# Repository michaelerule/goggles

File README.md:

# Goggles

Firmware and documentation for flicker-phosphene hallucination goggles. Some of the content here can be rendered as HTML, and a browsable website version of this repository can be [accessed through Github pages](https://michaelerule.github.io/goggles/).

This material follows earlier [blog posts](http://wealoneonearth.blogspot.co.uk/2009/09/how-to-build-goggles.html) outlining construction of do-it-yourself goggles to demonstrate the [flicker phosphene](http://journals.plos.org/ploscompbiol/article?id=10.1371/journal.pcbi.1002158) hallucination effect. A small batch of a [simplified re-design using welding goggles](http://treehovse.blogspot.co.uk) was produced a few years ago. 

Unless otherwise specified, media, text, and rendered outputs are licensed under the [Creative Commons Attribution Share Alike 4.0 license](https://choosealicense.com/licenses/cc-by-sa-4.0/) (CC BY-SA 4.0). Source code is licensed under the [GNU General Public License version 3.0](https://www.gnu.org/copyleft/gpl.html) (GPLv3). The CC BY-SA 4.0 is [one-way compatible](https://creativecommons.org/compatiblelicenses) with the GPLv3 license. The intent of this licensing choice is to encourage academic norms for citation and attribution. 

This project is published in the spirit (but not the letter) of the [tongue-and-cheek CRAPL license for academic code](http://matt.might.net/articles/crapl/CRAPL-LICENSE.txt). This is not a legal license as it contains internal inconsistencies (like forbidding users to exist). However, it contains a strong caution that this project has not been reviewed or prepared for use by the general public. If there is community interest in a specific subset of the project, please open an issue for improving the organization and documentation.

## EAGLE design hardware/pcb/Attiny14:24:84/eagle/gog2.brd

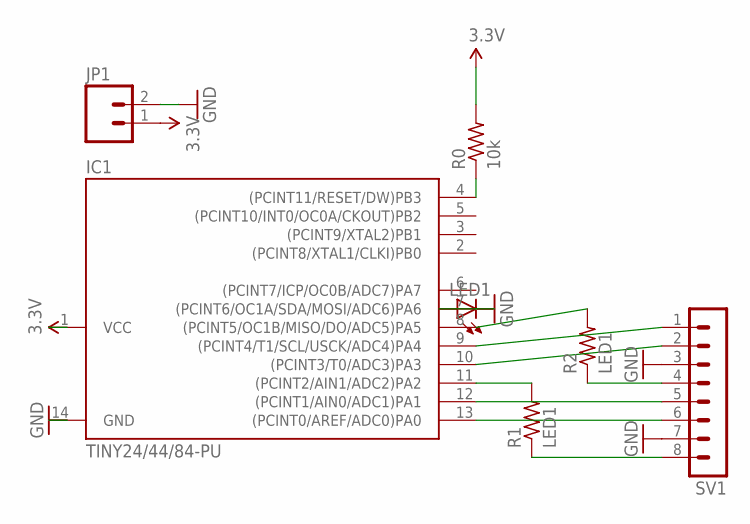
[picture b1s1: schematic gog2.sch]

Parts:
IC1: TINY24/44/84-PU; DIL14
JP1: M02; 1X02_LONGPADS
LED1: LED3MM
R0: 10k; 0207/7
R1, R2: LED1; 0207/7
SV1: MA08-1

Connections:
3.3V: IC1.1 (VCC), JP1.1, R0.2
GND: IC1.14 (GND), JP1.2, LED1.K (C), SV1.3, SV1.7
MISO: IC1.8 ((PCINT5/OC1B/MISO/DO/ADC5)PA5), R2.2
unnamed: IC1.7 ((PCINT6/OC1A/SDA/MOSI/ADC6)PA6), LED1.A
unnamed: IC1.11 ((PCINT2/AIN1/ADC2)PA2), R1.2
unnamed: R2.1, SV1.4
unnamed: R1.1, SV1.8
unnamed: IC1.13 ((PCINT0/AREF/ADC0)PA0), SV1.6
unnamed: IC1.12 ((PCINT1/AIN0/ADC1)PA1), SV1.5
unnamed: IC1.10 ((PCINT3/T0/ADC3)PA3), SV1.2
RESET: IC1.4 ((PCINT11/RESET/DW)PB3), R0.1
SCK: IC1.9 ((PCINT4/T1/SCL/USCK/ADC4)PA4), SV1.1

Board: 2 copper layers, 7 parts (1 on the bottom side), 12 nets, no tracks yet.

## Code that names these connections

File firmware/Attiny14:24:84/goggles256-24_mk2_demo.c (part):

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
/*              __ __
          VCC -|  U  |- GND
      BCK PB0 -|     |- PA0 G1
      SHU PB1 -|     |- PA1 B1
      RST PB3 -|     |- PA2 R1
      PLY PB2 -|     |- PA3 G2
      FWD PA7 -|     |- PA4 B2
      IND PA6 -|_____|- PA5 R2 
*/

#define HIGH   1
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
/*              __ __
          VCC -|  U  |- GND
      BCK PB0 -|     |- PA0 G1
      SHU PB1 -|     |- PA1 B1
      RST PB3 -|     |- PA2 R1
      PLY PB2 -|     |- PA3 G2
      FWD PA7 -|     |- PA4 B2
      IND PA6 -|_____|- PA5 R2 
*/

#define PORTA_IO_STATE (0x7f) // 0 1 11 1111 ( forward, indicator, RGBRGB )
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
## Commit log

2017-07-06 populates project
2017-07-09 updates project to CC BY-NC-SA 3.0 license
2017-07-11 move to CC BY-SA 4.0 with GPLv3 one-way compatibility license
2017-07-11 populate browsing links for github pages
2017-07-11 update readme to refer to original blog posts
2019-02-27 remove spurious file
